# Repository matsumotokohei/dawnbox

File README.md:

# DIY Leverless Arcade Controller

A custom, budget-friendly 19-button leverless arcade controller featuring an aluminum top plate with custom *Street Fighter 6* Alex artwork, Kailh MX mechanical switches (hot-swappable), MX-compatible keycaps, SK6812MINI-E RGB LEDs, a 0.96" I2C OLED display, and an exposed custom PCB design secured with M3 standoffs. Fully routed in KiCad, manufactured by JLCPCB, and powered by Raspberry Pi Pico with GP2040-CE.

## 📸 Gallery / Previews

### Keyboard Layout

### Main PCB

| Top View (Front) | Bottom View (Back) |
| :---: | :---: |
|  |  |

### Aluminum Top Plate

| Top View (Front with Alex Artwork) | Bottom View (Back) |
| :---: | :---: |
|  |  |

## 📌 Project Overview

This project focuses on building a high-performance, low-latency, and cost-effective 19-button leverless controller from scratch. By wiring 19 switches directly to the Raspberry Pi Pico without a diode matrix, this design achieves instantaneous input response. The controller features a rigid aluminum top plate detailed with custom silkscreen character artwork, a 0.96-inch status display, and a sleek, minimalist exposed PCB design held together firmly by industrial-standard M3 mounting hardware.

## 🎯 Key Features & Technical Specs

*   **Custom Alex (SF6) Artwork**: The aluminum top plate features high-detail silkscreen artwork of **Alex from Street Fighter 6**, making it a truly personalized piece of hardware.
*   **19-Button Layout**: A comprehensive 19-button matrix designed for modern fighting games and macro layouts.
*   **Firmware**: Powered by [GP2040-CE](https://gp2040-ce.info), offering ultra-low latency and multi-platform compatibility.
*   **Controller**: Uses a **Raspberry Pi Pico** (RP2040) as the main MCU.
*   **No Diodes (Direct Connection)**: All 19 switches are wired directly to individual GPIO pins on the Pico, maximizing responsiveness and avoiding ghosting without a matrix.
*   **Aluminum Top Plate**: Utilizes an aluminum plate manufactured by **JLCPCB** as the top enclosure for a premium, rigid, and durable finish.
*   **Exposed PCB Case Design**: Minimalist aesthetic with exposed sides and bottom, utilizing heavy-duty **M3 spacers/standoffs** directly attached via M3 mounting holes routed into the main board and top plate.
*   **Hot-Swappable Switches**: Uses **Kailh MX-compatible switches** with **Kailh hot-swap sockets**, allowing easy switch replacement without soldering.
*   **Keycaps**: Designed specifically for standard **MX-compatible keycaps**.
*   **0.96" I2C OLED Display**: Features an onboard **128x64 OLED screen (SSD1306)** connected via a dedicated 4-pin header interface to display real-time input history, active profiles, SOCD modes, and connection status. (No external pull-up resistors required).  (Optional)
*   **RGB LED Power & Stability**: LEDs are powered directly via the Pico's **VSYS pin** (5V). The power rail is stabilized with a **47μF SMD 1206 (3216)** bulk capacitor alongside individual **0.1μF SMD 1206 (3216)** decoupling capacitors for each LED to handle voltage fluctuations.  (Optional)
*   **Level Shifter Circuit**: Integrates a **74HC4050** hex buffer to safely step up the Pico's 3.3V data signal to 5V for reliable LED operation. (Optional)

## 📦 Design Libraries & Footprints

The following external libraries and specific footprints were used in KiCad for this project:

*   **Main PCB Switch Sockets**: 
    *   Library: [daprice/keyswitches.pretty](https://github.com)
    *   Footprint: `Kailh_socket_MX.kicad_mod` (For MX hotswap sockets)
*   **Top Plate Switch Cutouts**:
    *   Library: [foostan/kbd (kbd.pretty)](https://github.com)
    *   Footprint: `keyswitch_hole.kicad_mod` (For precise aluminum switch plate holes)

## 🛠️ Work Process & Status

### 1. Keyboard Layout & Artwork Design
*   Created a custom 19-button ergonomic layout using [Keyboard Layout Editor (KLE)](http://keyboard-layout.org).
*   Optimized button spacing for comfortable hand placement and optimal reaction times.
*   Prepared vector line art of *Street Fighter 6* Alex to be imported into the KiCad silkscreen layer.

### 2. Schematic & PCB / Plate Design (KiCad)
*   Imported layout data and mapped 19 direct GPIO lines from the Pico to each switch in **KiCad**.
*   Added a 4-pin male pin header (GND, VCC, SCL, SDA) for the 0.96" OLED module.
*   Configured the 74HC4050 level shifter circuit and added the 47μF bulk capacitor (1206 size) near the VSYS power entry point, with individual 0.1μF 1206 decoupling capacitors routed close to each LED.
*   Placed precise **M3 mounting holes** strategically across the board to ensure rigid structural support.
*   Designed the aluminum top enclosure plate using the exact same switch layout and M3 hole coordinates, then overlaid the Alex artwork onto the silkscreen layer.
*   Generated Gerber, drill, and production files optimized for JLCPCB specifications (both for the main PCB and the aluminum plate).

### 3. Manufacturing (JLCPCB)
*   Uploaded Gerber files to **JLCPCB** for both main PCB fabrication and aluminum plate cutting (specified as an Aluminum PCB layer with custom silkscreen).
*   *(Optional)* Utilized JLCPCB SMT Assembly service for surface-mount components (74HC4050, SK6812MINI-E, 1206 Capacitors).

### 4. Assembly & Firmware Flashing
*   *Next Step*: Solder remaining components (Kailh MX hot-swap sockets, Raspberry Pi Pico, 4-pin Male Pin Header).
*   *Next Step*: Flash the latest GP2040-CE firmware onto the Pico.
*   *Next Step*: Assemble the structural **M3 spacers/standoffs** onto the main PCB.
*   *Next Step*: Mount the custom Alex aluminum top plate using M3 screws, pop in the 19 Kailh MX switches, plug the 0.96" OLED display into the pin header, and attach the MX-compatible keycaps.
*   *Next Step*: Configure pin mappings, I2C display settings, and LED profiles via the GP2040-CE Web Configurator.

## 🧱 Bill of Materials (BOM)

| Component           | Description                                      | Qty   | Note |
| :---                | :---                                             | :---  | :--- |
| **Main PCB**        | Custom designed board manufactured by **JLCPCB** | 1     | -    |
| **Top Plate**       | Custom Aluminum plate with Alex artwork (JLCPCB) | 1     | -    |
| **MCU**             | Raspberry Pi Pico (RP2040)                       | 1     | -    |
| **Sockets**         | Kailh MX Hot-swap Sockets                        | 19    | -    |
| **Keycaps**         | MX-compatible keycaps                            | 19    | -    |
| **Switches**        | Kailh MX-compatible Mechanical Switches          | 19    | -    |
| **M3 Standoffs**    | Female-Female Spacers for enclosure stability    | 8     | -    |
| **M3 Screws**       | Screws to secure the PCB and Aluminum Top Plate  | 16    | -    |
| **IC**              | 74HC4050 (Level Shifter for LEDs)                | 1     | Optional |
| **LEDs**            | SK6812MINI-E (Addressable RGB)                   | 19    | Optional |
| **Bulk Cap**        | 47μF SMD 1206 (3216 Metric) Ceramic Capacitor    | 1     | Optional |
| **Decoupling Caps for LEDs** | 0.1μF SMD 1206 (3216 Metric) Ceramic Capacitors | 19   | Optional |
| **Decoupling Caps for 74HC** | 0.1μF SMD 1206 (3216 Metric) Ceramic Capacitors | 1    | Optional |
| **Decoupling Caps for MCU**  | 47μF SMD 1206 (3216 Metric) Ceramic Capacitors  | 1    | Optional |
| **Display**         | 0.96" I2C OLED Module (128x64 SSD1306 / 4-pin)   | 1     | Optional |
| **Header Pins**     | 1x4 Male Pin Header (2.54mm pitch) for OLED      | 1     | Optional |

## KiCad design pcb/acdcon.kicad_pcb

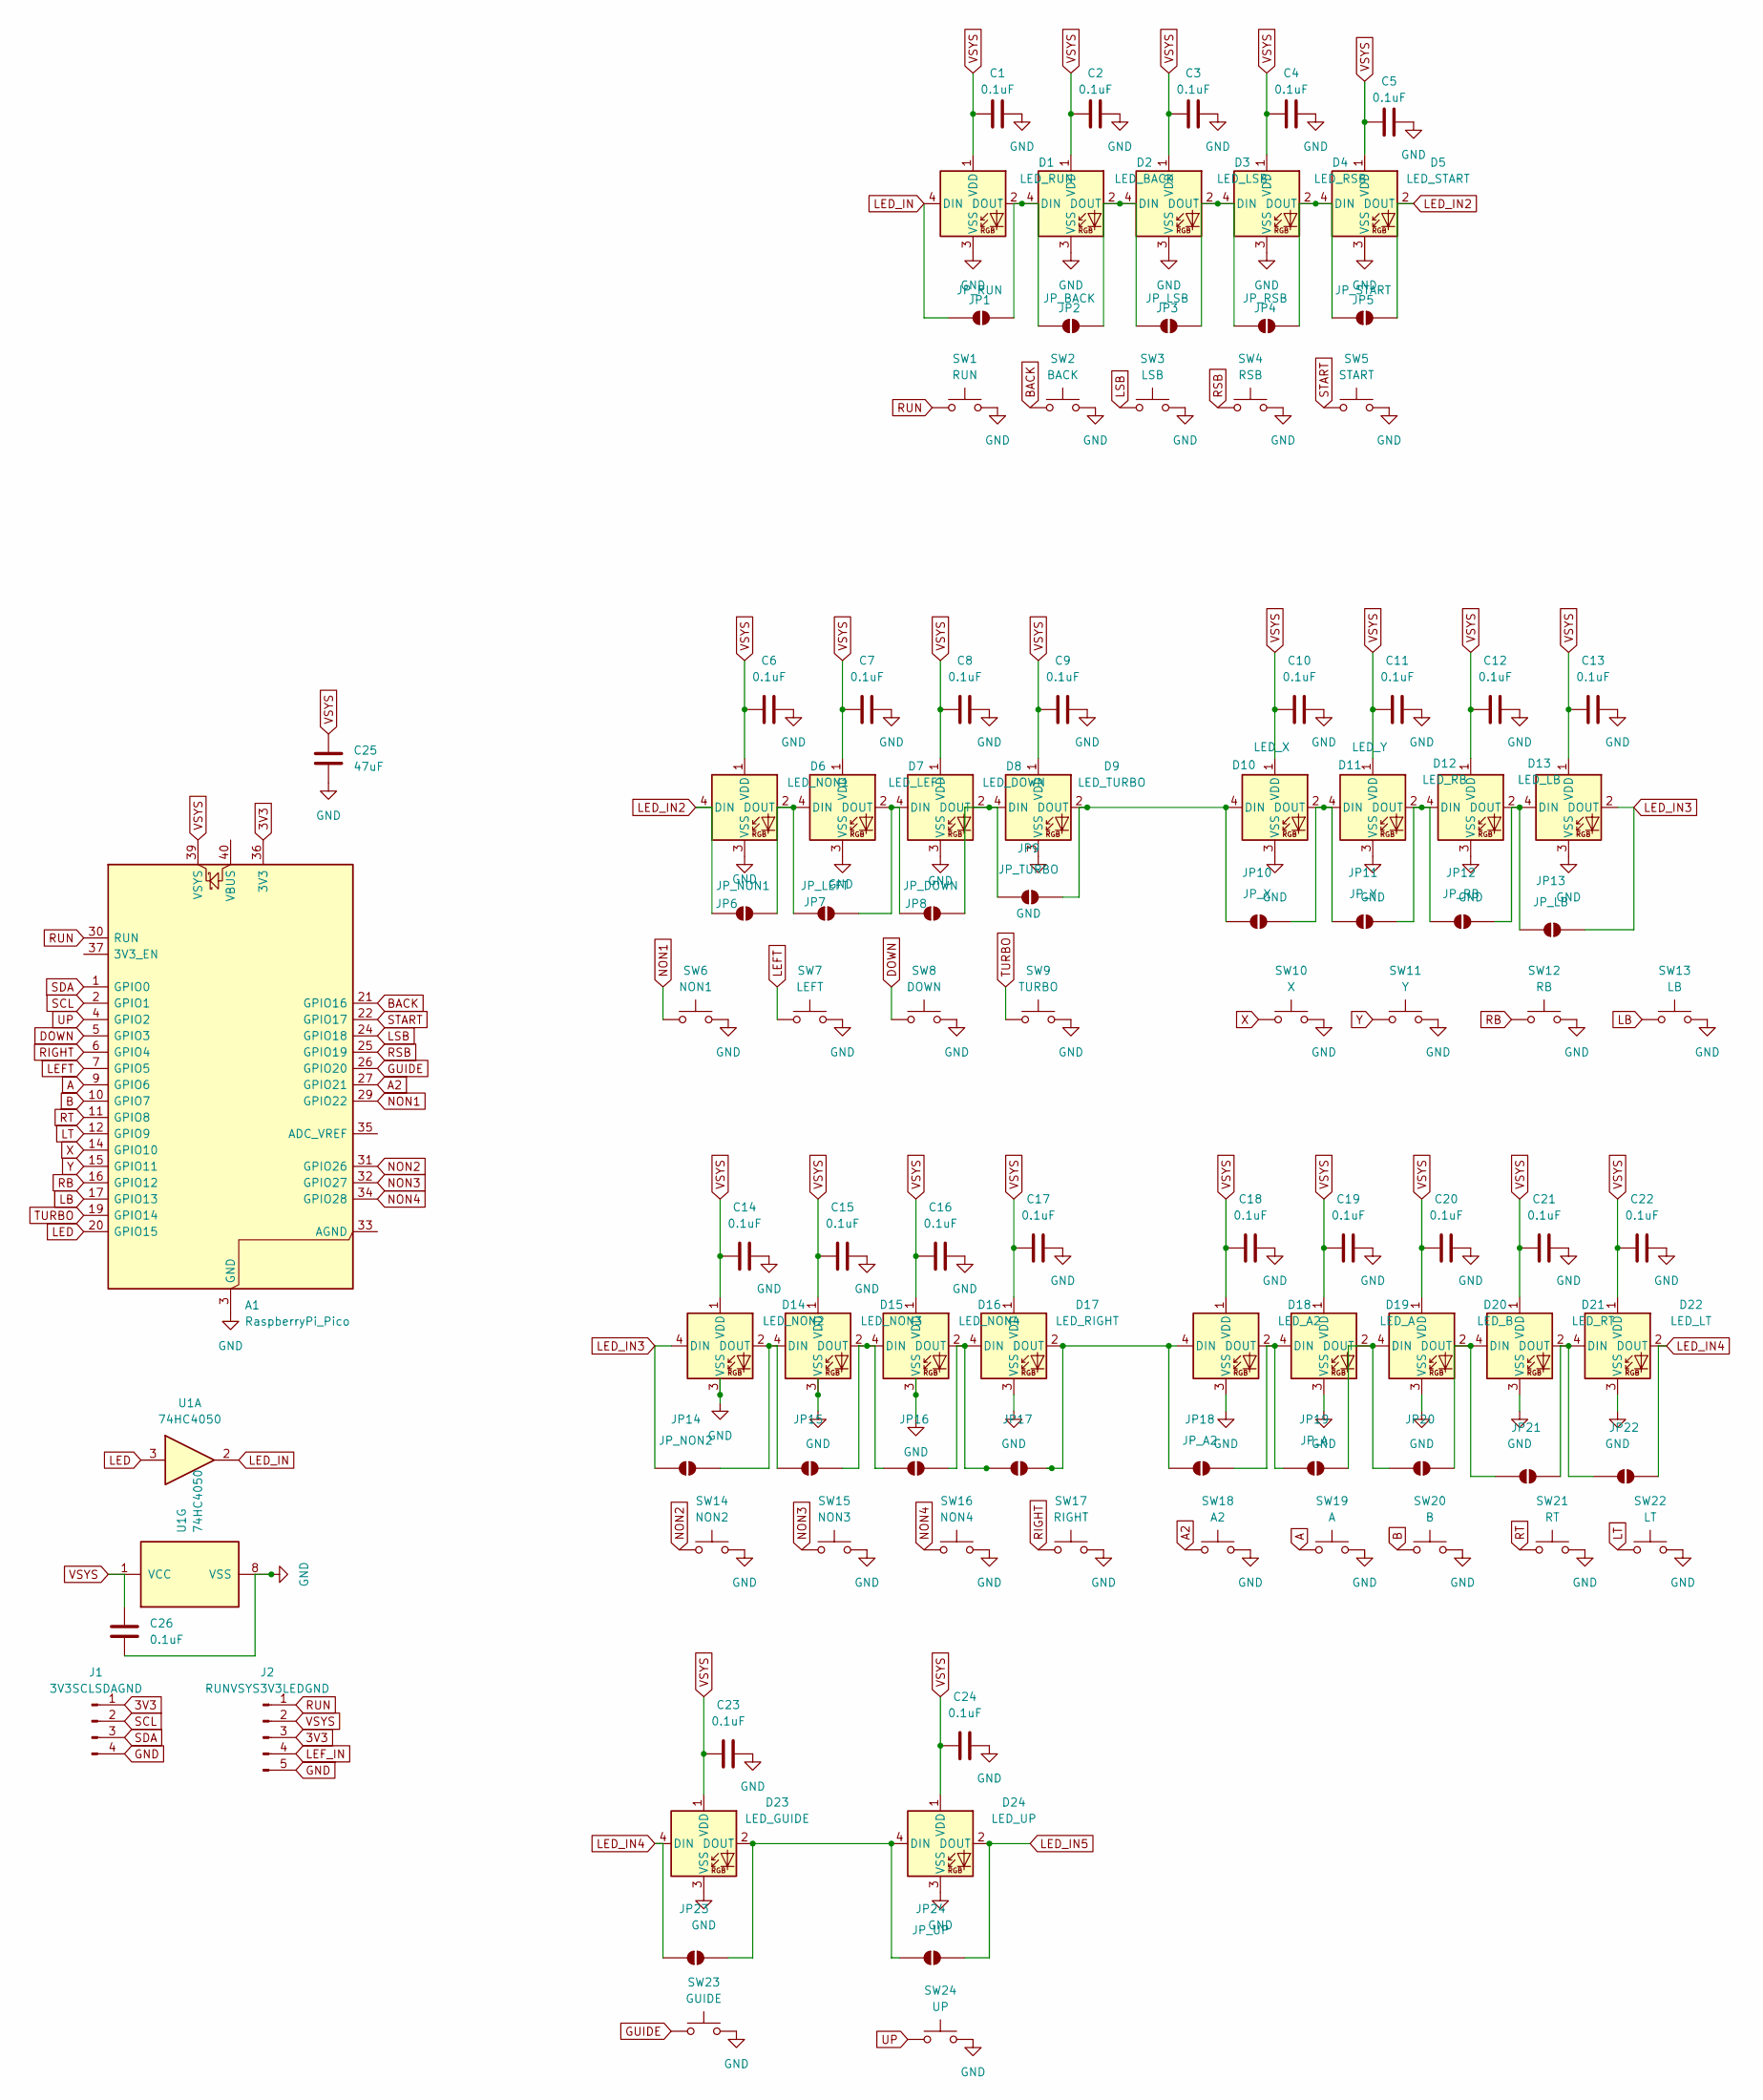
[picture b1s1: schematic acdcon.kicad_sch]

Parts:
A1: RaspberryPi_Pico; RaspberryPi_Pico_Common_THT
C1, C2, C3, C4, C5, C6, C7, C8, C9, C10, C11, C12, C13, C14, C15, C16, C17, C18, C19, C20, C21, C22, C23, C24, C26: 0.1uF; C_1206_3216Metric
C25: 47uF; C_1206_3216Metric
D1: LED_RUN; LED_SK6812MINI-E_3.2x2.8mm_P1.5mm_ReverseMount
D2: LED_BACK; LED_SK6812MINI-E_3.2x2.8mm_P1.5mm_ReverseMount
D3: LED_LSB; LED_SK6812MINI-E_3.2x2.8mm_P1.5mm_ReverseMount
D4: LED_RSB; LED_SK6812MINI-E_3.2x2.8mm_P1.5mm_ReverseMount
D5: LED_START; LED_SK6812MINI-E_3.2x2.8mm_P1.5mm_ReverseMount
D6: LED_NON1; LED_SK6812MINI-E_3.2x2.8mm_P1.5mm_ReverseMount
D7: LED_LEFT; LED_SK6812MINI-E_3.2x2.8mm_P1.5mm_ReverseMount
D8: LED_DOWN; LED_SK6812MINI-E_3.2x2.8mm_P1.5mm_ReverseMount
D9: LED_TURBO; LED_SK6812MINI-E_3.2x2.8mm_P1.5mm_ReverseMount
D10: LED_X; LED_SK6812MINI-E_3.2x2.8mm_P1.5mm_ReverseMount
D11: LED_Y; LED_SK6812MINI-E_3.2x2.8mm_P1.5mm_ReverseMount
D12: LED_RB; LED_SK6812MINI-E_3.2x2.8mm_P1.5mm_ReverseMount
D13: LED_LB; LED_SK6812MINI-E_3.2x2.8mm_P1.5mm_ReverseMount
D14: LED_NON2; LED_SK6812MINI-E_3.2x2.8mm_P1.5mm_ReverseMount
D15: LED_NON3; LED_SK6812MINI-E_3.2x2.8mm_P1.5mm_ReverseMount
D16: LED_NON4; LED_SK6812MINI-E_3.2x2.8mm_P1.5mm_ReverseMount
D17: LED_RIGHT; LED_SK6812MINI-E_3.2x2.8mm_P1.5mm_ReverseMount
D18: LED_A2; LED_SK6812MINI-E_3.2x2.8mm_P1.5mm_ReverseMount
D19: LED_A; LED_SK6812MINI-E_3.2x2.8mm_P1.5mm_ReverseMount
D20: LED_B; LED_SK6812MINI-E_3.2x2.8mm_P1.5mm_ReverseMount
D21: LED_RT; LED_SK6812MINI-E_3.2x2.8mm_P1.5mm_ReverseMount
D22: LED_LT; LED_SK6812MINI-E_3.2x2.8mm_P1.5mm_ReverseMount
D23: LED_GUIDE; LED_SK6812MINI-E_3.2x2.8mm_P1.5mm_ReverseMount
D24: LED_UP; LED_SK6812MINI-E_3.2x2.8mm_P1.5mm_ReverseMount
J1: 3V3SCLSDAGND; PinHeader_1x04_P2.54mm_Vertical
J2: RUNVSYS3V3LEDGND; PinHeader_1x05_P2.54mm_Vertical
JP1: JP_RUN; SolderJumper-2_P1.3mm_Open_RoundedPad1.0x1.5mm
JP2: JP_BACK; SolderJumper-2_P1.3mm_Open_RoundedPad1.0x1.5mm
JP3: JP_LSB; SolderJumper-2_P1.3mm_Open_RoundedPad1.0x1.5mm
JP4: JP_RSB; SolderJumper-2_P1.3mm_Open_RoundedPad1.0x1.5mm
JP5: JP_START; SolderJumper-2_P1.3mm_Open_RoundedPad1.0x1.5mm
JP6: JP_NON1; SolderJumper-2_P1.3mm_Open_RoundedPad1.0x1.5mm
JP7: JP_LEFT; SolderJumper-2_P1.3mm_Open_RoundedPad1.0x1.5mm
JP8: JP_DOWN; SolderJumper-2_P1.3mm_Open_RoundedPad1.0x1.5mm
JP9: JP_TURBO; SolderJumper-2_P1.3mm_Open_RoundedPad1.0x1.5mm
JP10: JP_X; SolderJumper-2_P1.3mm_Open_RoundedPad1.0x1.5mm
JP11: JP_Y; SolderJumper-2_P1.3mm_Open_RoundedPad1.0x1.5mm
JP12: JP_RB; SolderJumper-2_P1.3mm_Open_RoundedPad1.0x1.5mm
JP13: JP_LB; SolderJumper-2_P1.3mm_Open_RoundedPad1.0x1.5mm
JP14: JP_NON2; SolderJumper-2_P1.3mm_Open_RoundedPad1.0x1.5mm
JP15: JP_NON3; SolderJumper-2_P1.3mm_Open_RoundedPad1.0x1.5mm
JP16: JP_NON4; SolderJumper-2_P1.3mm_Open_RoundedPad1.0x1.5mm
JP17: JP_RIGHT; SolderJumper-2_P1.3mm_Open_RoundedPad1.0x1.5mm
JP18: JP_A2; SolderJumper-2_P1.3mm_Open_RoundedPad1.0x1.5mm
JP19: JP_A; SolderJumper-2_P1.3mm_Open_RoundedPad1.0x1.5mm
JP20: JP_B; SolderJumper-2_P1.3mm_Open_RoundedPad1.0x1.5mm
JP21: JP_RT; SolderJumper-2_P1.3mm_Open_RoundedPad1.0x1.5mm
JP22: JP_LT; SolderJumper-2_P1.3mm_Open_RoundedPad1.0x1.5mm
JP23: JP_GUIDE; SolderJumper-2_P1.3mm_Open_RoundedPad1.0x1.5mm
JP24: JP_UP; SolderJumper-2_P1.3mm_Open_RoundedPad1.0x1.5mm
SW1: RUN; Kailh_socket_MX
SW2: BACK; Kailh_socket_MX
SW3: LSB; Kailh_socket_MX
SW4: RSB; Kailh_socket_MX
SW5: START; Kailh_socket_MX
SW6: NON1; Kailh_socket_MX
SW7: LEFT; Kailh_socket_MX
SW8: DOWN; Kailh_socket_MX
SW9: TURBO; Kailh_socket_MX
SW10: X; Kailh_socket_MX
SW11: Y; Kailh_socket_MX
SW12: RB; Kailh_socket_MX
SW13: LB; Kailh_socket_MX
SW14: NON2; Kailh_socket_MX
SW15: NON3; Kailh_socket_MX
SW16: NON4; Kailh_socket_MX
SW17: RIGHT; Kailh_socket_MX
SW18: A2; Kailh_socket_MX
SW19: A; Kailh_socket_MX
SW20: B; Kailh_socket_MX
SW21: RT; Kailh_socket_MX
SW22: LT; Kailh_socket_MX
SW23: GUIDE; Kailh_socket_MX
SW24: UP; Kailh_socket_MX
U1: 74HC4050; DIP-16_W7.62mm

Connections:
3V3: A1.36 (3V3), J1.1, J2.3
A: A1.9 (GPIO6), SW19.1
A2: A1.27 (GPIO21), SW18.1
B: A1.10 (GPIO7), SW20.1
BACK: A1.21 (GPIO16), SW2.1
DOWN: A1.5 (GPIO3), SW8.1
GND: A1.3 (GND), A1.8 (GND), A1.13 (GND), A1.18 (GND), A1.23 (GND), A1.28 (GND), A1.38 (GND), C1.2, C2.2, C3.2, C4.2, C5.2, C6.2, C7.2, C8.2, C9.2, C10.2, C11.2, C12.2, C13.2, C14.2, C15.2, C16.2, C17.2, C18.2, C19.2, C20.2, C21.2, C22.2, C23.2, C24.2, C25.2, C26.2, D1.3 (VSS), D2.3 (VSS), D3.3 (VSS), D4.3 (VSS), D5.3 (VSS), D6.3 (VSS), D7.3 (VSS), D8.3 (VSS), D9.3 (VSS), D10.3 (VSS), D11.3 (VSS), D12.3 (VSS), D13.3 (VSS), D14.3 (VSS), D15.3 (VSS), D16.3 (VSS), D17.3 (VSS), D18.3 (VSS), D19.3 (VSS), D20.3 (VSS), D21.3 (VSS), D22.3 (VSS), D23.3 (VSS), D24.3 (VSS), J1.4, J2.5, SW1.2, SW2.2, SW3.2, SW4.2, SW5.2, SW6.2, SW7.2, SW8.2, SW9.2, SW10.2, SW11.2, SW12.2, SW13.2, SW14.2, SW15.2, SW16.2, SW17.2, SW18.2, SW19.2, SW20.2, SW21.2, SW22.2, SW23.2, SW24.2, U1.8 (VSS)
GUIDE: A1.26 (GPIO20), SW23.1
LB: A1.17 (GPIO13), SW13.1
LED: A1.20 (GPIO15), U1.3
LED_IN: D1.4 (DIN), JP1.1 (A), U1.2
LED_IN2: D5.2 (DOUT), D6.4 (DIN), JP5.2 (B), JP6.1 (A)
LED_IN3: D13.2 (DOUT), D14.4 (DIN), JP13.2 (B), JP14.1 (A)
LED_IN4: D22.2 (DOUT), D23.4 (DIN), JP22.2 (B), JP23.1 (A)
LED_IN5: D24.2 (DOUT), JP24.2 (B)
LEFT: A1.7 (GPIO5), SW7.1
LEF_IN: J2.4
LSB: A1.24 (GPIO18), SW3.1
LT: A1.12 (GPIO9), SW22.1
NON1: A1.29 (GPIO22), SW6.1
NON2: A1.31 (GPIO26), SW14.1
NON3: A1.32 (GPIO27), SW15.1
NON4: A1.34 (GPIO28), SW16.1
unnamed: D1.2 (DOUT), D2.4 (DIN), JP1.2 (B), JP2.1 (A)
unnamed: D2.2 (DOUT), D3.4 (DIN), JP2.2 (B), JP3.1 (A)
unnamed: D3.2 (DOUT), D4.4 (DIN), JP3.2 (B), JP4.1 (A)
unnamed: D4.2 (DOUT), D5.4 (DIN), JP4.2 (B), JP5.1 (A)
unnamed: D6.2 (DOUT), D7.4 (DIN), JP6.2 (B), JP7.1 (A)
unnamed: D7.2 (DOUT), D8.4 (DIN), JP7.2 (B), JP8.1 (A)
unnamed: D8.2 (DOUT), D9.4 (DIN), JP8.2 (B), JP9.1 (A)
unnamed: D9.2 (DOUT), D10.4 (DIN), JP9.2 (B), JP10.1 (A)
unnamed: D10.2 (DOUT), D11.4 (DIN), JP10.2 (B), JP11.1 (A)
unnamed: D11.2 (DOUT), D12.4 (DIN), JP11.2 (B), JP12.1 (A)
unnamed: D12.2 (DOUT), D13.4 (DIN), JP12.2 (B), JP13.1 (A)
unnamed: D14.2 (DOUT), D15.4 (DIN), JP14.2 (B), JP15.1 (A)
unnamed: D15.2 (DOUT), D16.4 (DIN), JP15.2 (B), JP16.1 (A)
unnamed: D16.2 (DOUT), D17.4 (DIN), JP16.2 (B), JP17.1 (A)
unnamed: D17.2 (DOUT), D18.4 (DIN), JP17.2 (B), JP18.1 (A)
unnamed: D18.2 (DOUT), D19.4 (DIN), JP18.2 (B), JP19.1 (A)
unnamed: D19.2 (DOUT), D20.4 (DIN), JP19.2 (B), JP20.1 (A)
unnamed: D20.2 (DOUT), D21.4 (DIN), JP20.2 (B), JP21.1 (A)
unnamed: D21.2 (DOUT), D22.4 (DIN), JP21.2 (B), JP22.1 (A)
unnamed: D23.2 (DOUT), D24.4 (DIN), JP23.2 (B), JP24.1 (A)
RB: A1.16 (GPIO12), SW12.1
RIGHT: A1.6 (GPIO4), SW17.1
RSB: A1.25 (GPIO19), SW4.1
RT: A1.11 (GPIO8), SW21.1
RUN: A1.30 (RUN), J2.1, SW1.1
SCL: A1.2 (GPIO1), J1.2
SDA: A1.1 (GPIO0), J1.3
START: A1.22 (GPIO17), SW5.1
TURBO: A1.19 (GPIO14), SW9.1
UP: A1.4 (GPIO2), SW24.1
VSYS: A1.39 (VSYS), C1.1, C2.1, C3.1, C4.1, C5.1, C6.1, C7.1, C8.1, C9.1, C10.1, C11.1, C12.1, C13.1, C14.1, C15.1, C16.1, C17.1, C18.1, C19.1, C20.1, C21.1, C22.1, C23.1, C24.1, C25.1, C26.1, D1.1 (VDD), D2.1 (VDD), D3.1 (VDD), D4.1 (VDD), D5.1 (VDD), D6.1 (VDD), D7.1 (VDD), D8.1 (VDD), D9.1 (VDD), D10.1 (VDD), D11.1 (VDD), D12.1 (VDD), D13.1 (VDD), D14.1 (VDD), D15.1 (VDD), D16.1 (VDD), D17.1 (VDD), D18.1 (VDD), D19.1 (VDD), D20.1 (VDD), D21.1 (VDD), D22.1 (VDD), D23.1 (VDD), D24.1 (VDD), J2.2, U1.1 (VCC)
X: A1.14 (GPIO10), SW10.1
Y: A1.15 (GPIO11), SW11.1

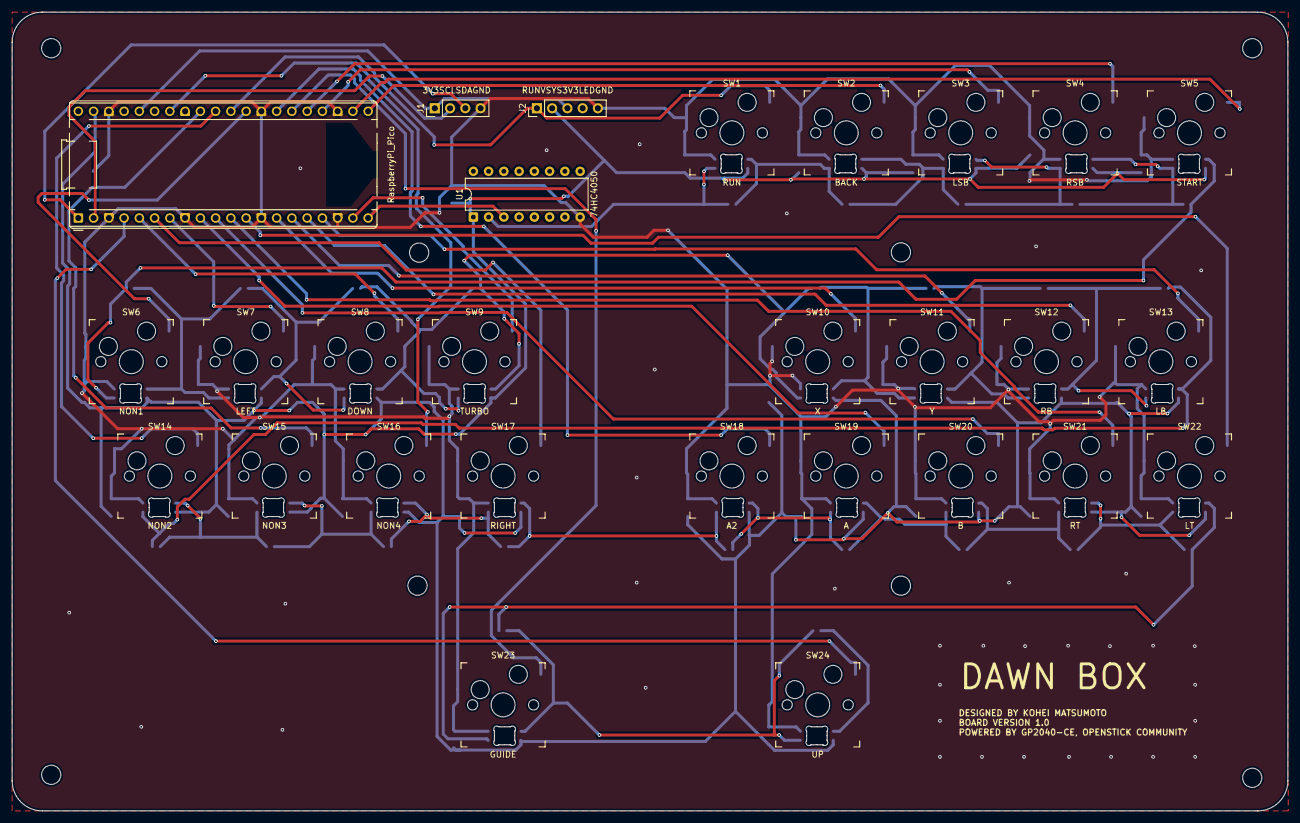
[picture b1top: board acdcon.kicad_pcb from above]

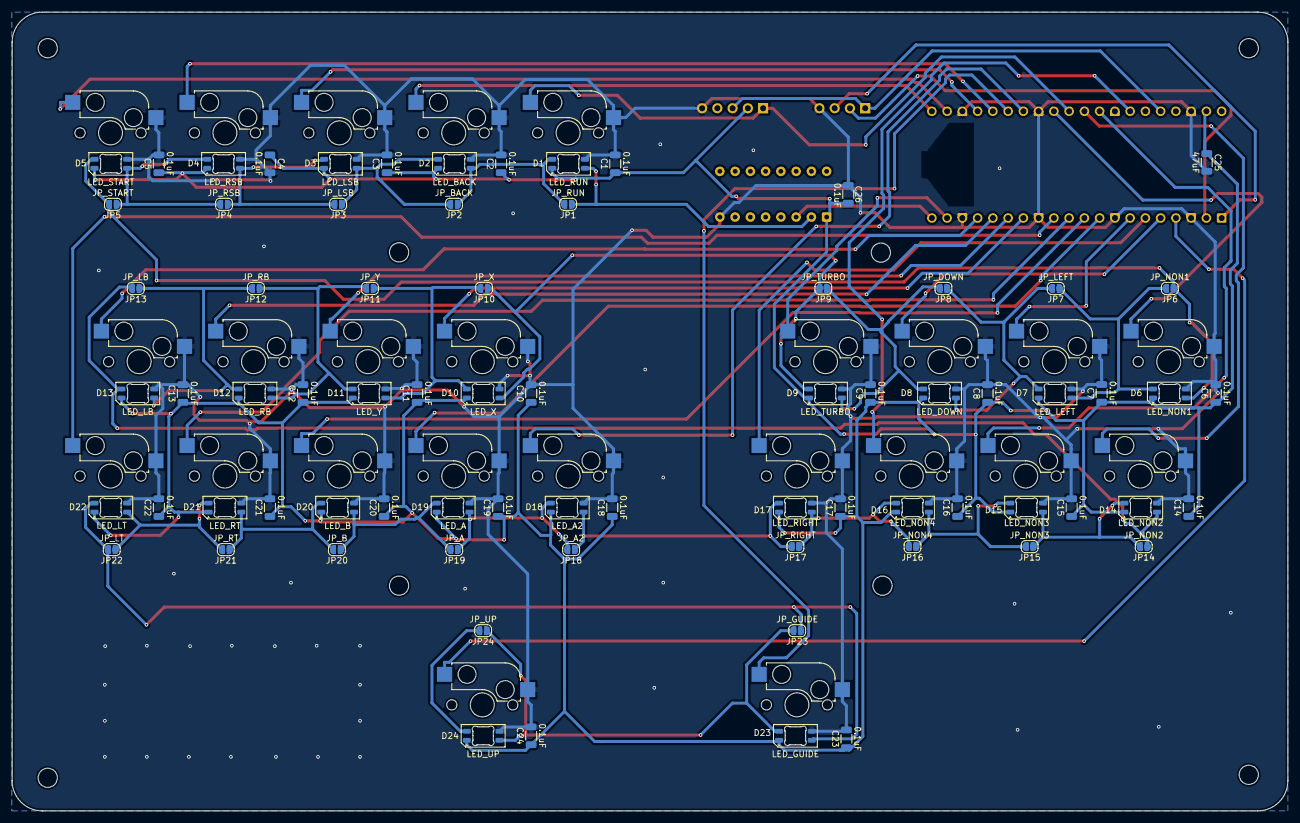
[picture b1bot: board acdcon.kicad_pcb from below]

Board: 2 copper layers, 212.4 x 133.0 mm, 110 parts (74 on the bottom side), 55 nets.

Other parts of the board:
Hole1, Hole2, Hole3, Hole4, Hole5, Hole6, Hole7, Hole8: MountingHole_3.2mm_M3

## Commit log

2026-05-17 Init: Create project and add custom 24-button leverless controller README
2026-05-17 Update BOM with specific hardware quantities
2026-05-17 Add optional hardware
2026-05-17 Update Keyboard Layout
2026-05-17 Update 19-button leverless controller
